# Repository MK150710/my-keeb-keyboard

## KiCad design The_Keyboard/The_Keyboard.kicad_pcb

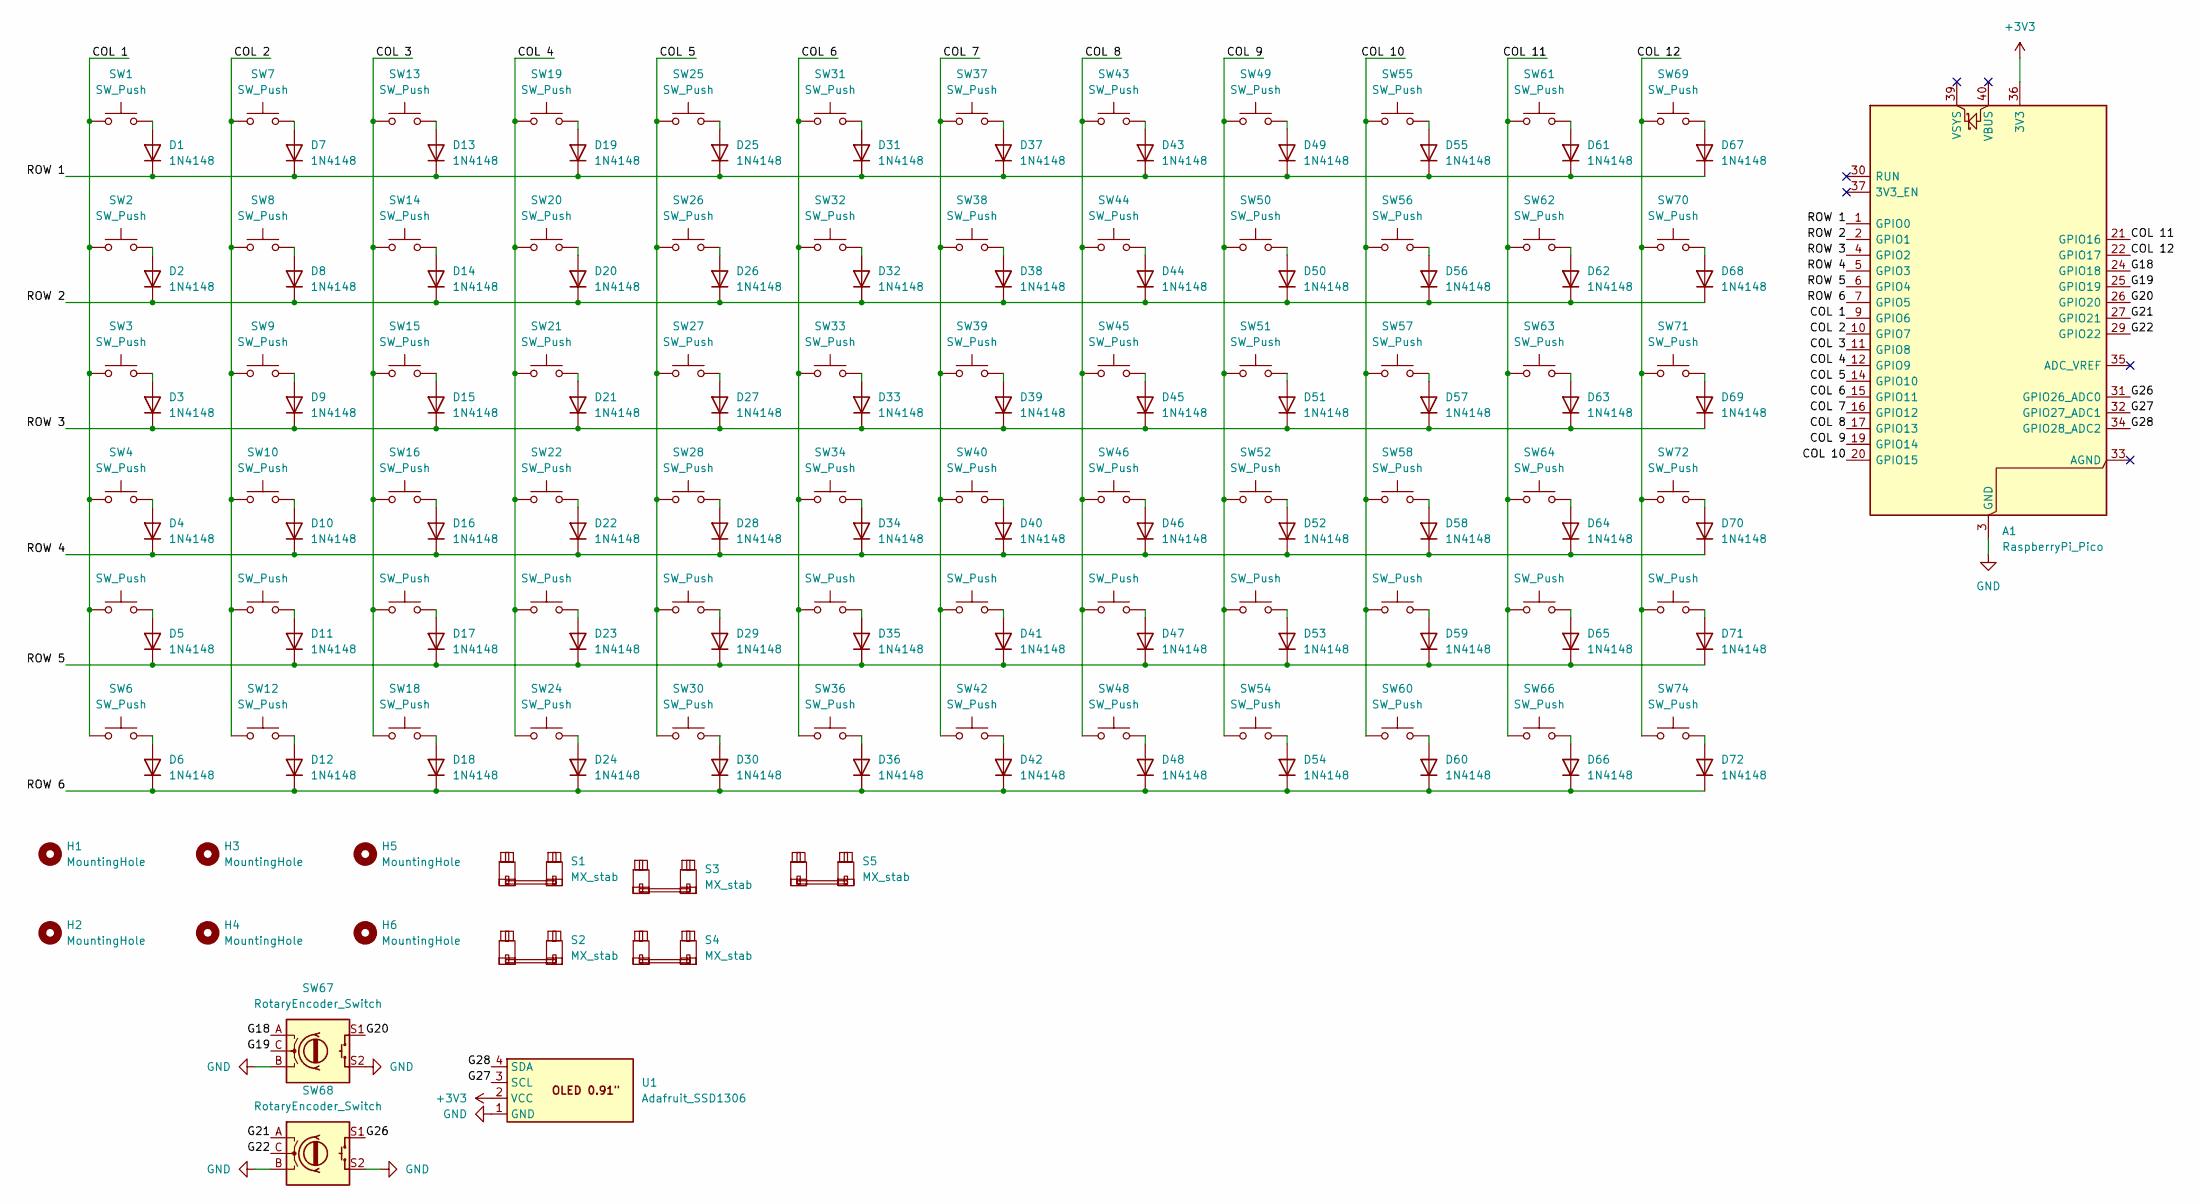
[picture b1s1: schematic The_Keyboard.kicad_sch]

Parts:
A1: RaspberryPi_Pico; RaspberryPi_Pico_Common_THT
D1, D2, D3, D4, D5, D6, D7, D8, D9, D10, D11, D12, D13, D14, D15, D16, D17, D18, D19, D20, D21, D22, D23, D24, D25, D26, D27, D28, D29, D30, D31, D32, D33, D34, D35, D36, D37, D38, D39, D40, D41, D42, D43, D44, D45, D46, D47, D48, D49, D50, D51, D52, D53, D54, D55, D56, D57, D58, D59, D60, D61, D62, D63, D64, D65, D66, D67, D68, D69, D70, D71, D72: 1N4148; D_DO-35_SOD27_P7.62mm_Horizontal
H1, H2, H3, H4, H5, H6: MountingHole; MountingHole_3.2mm_M3
S1, S3, S5: MX_stab; STAB_MX_2u
S2: MX_stab; STAB_MX_2.25u
S4: MX_stab; STAB_MX_P_6.25u
SW1, SW2, SW3, SW4, SW5, SW6, SW7, SW8, SW9, SW10, SW11, SW12, SW13, SW14, SW15, SW16, SW17, SW18, SW19, SW20, SW21, SW22, SW23, SW24, SW25, SW26, SW27, SW28, SW29, SW30, SW31, SW32, SW33, SW34, SW35, SW36, SW37, SW38, SW39, SW40, SW41, SW42, SW43, SW44, SW45, SW46, SW47, SW48, SW49, SW50, SW51, SW52, SW53, SW54, SW55, SW56, SW57, SW58, SW59, SW60, SW61, SW62, SW63, SW64, SW65, SW66, SW69, SW70, SW71, SW72, SW73, SW74: SW_Push; SW_MX_1u
SW67, SW68: RotaryEncoder_Switch; ROT_Alps_EC11E-Switch
U1: Adafruit_SSD1306; ER_OLEDM0.91_1x-I2C

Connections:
+3V3: A1.36 (3V3), U1.2 (VCC)
/COL 1: A1.9 (GPIO6), SW1.1, SW2.1, SW3.1, SW4.1, SW5.1, SW6.1
/COL 2: A1.10 (GPIO7), SW7.1, SW8.1, SW9.1, SW10.1, SW11.1, SW12.1
/COL 3: A1.11 (GPIO8), SW13.1, SW14.1, SW15.1, SW16.1, SW17.1, SW18.1
/COL 4: A1.12 (GPIO9), SW19.1, SW20.1, SW21.1, SW22.1, SW23.1, SW24.1
/COL 5: A1.14 (GPIO10), SW25.1, SW26.1, SW27.1, SW28.1, SW29.1, SW30.1
/COL 6: A1.15 (GPIO11), SW31.1, SW32.1, SW33.1, SW34.1, SW35.1, SW36.1
/COL 7: A1.16 (GPIO12), SW37.1, SW38.1, SW39.1, SW40.1, SW41.1, SW42.1
/COL 8: A1.17 (GPIO13), SW43.1, SW44.1, SW45.1, SW46.1, SW47.1, SW48.1
/COL 9: A1.19 (GPIO14), SW49.1, SW50.1, SW51.1, SW52.1, SW53.1, SW54.1
/COL 10: A1.20 (GPIO15), SW55.1, SW56.1, SW57.1, SW58.1, SW59.1, SW60.1
/COL 11: A1.21 (GPIO16), SW61.1, SW62.1, SW63.1, SW64.1, SW65.1, SW66.1
/COL 12: A1.22 (GPIO17), SW69.1, SW70.1, SW71.1, SW72.1, SW73.1, SW74.1
/G18: A1.24 (GPIO18), SW67.A
/G19: A1.25 (GPIO19), SW67.C
/G20: A1.26 (GPIO20), SW67.S1
/G21: A1.27 (GPIO21), SW68.A
/G22: A1.29 (GPIO22), SW68.C
/G26: A1.31 (GPIO26_ADC0), SW68.S1
/G27: A1.32 (GPIO27_ADC1), U1.3 (SCL)
/G28: A1.34 (GPIO28_ADC2), U1.4 (SDA)
/ROW 1: A1.1 (GPIO0), D1.1 (K), D7.1 (K), D13.1 (K), D19.1 (K), D25.1 (K), D31.1 (K), D37.1 (K), D43.1 (K), D49.1 (K), D55.1 (K), D61.1 (K), D67.1 (K)
/ROW 2: A1.2 (GPIO1), D2.1 (K), D8.1 (K), D14.1 (K), D20.1 (K), D26.1 (K), D32.1 (K), D38.1 (K), D44.1 (K), D50.1 (K), D56.1 (K), D62.1 (K), D68.1 (K)
/ROW 3: A1.4 (GPIO2), D3.1 (K), D9.1 (K), D15.1 (K), D21.1 (K), D27.1 (K), D33.1 (K), D39.1 (K), D45.1 (K), D51.1 (K), D57.1 (K), D63.1 (K), D69.1 (K)
/ROW 4: A1.5 (GPIO3), D4.1 (K), D10.1 (K), D16.1 (K), D22.1 (K), D28.1 (K), D34.1 (K), D40.1 (K), D46.1 (K), D52.1 (K), D58.1 (K), D64.1 (K), D70.1 (K)
/ROW 5: A1.6 (GPIO4), D5.1 (K), D11.1 (K), D17.1 (K), D23.1 (K), D29.1 (K), D35.1 (K), D41.1 (K), D47.1 (K), D53.1 (K), D59.1 (K), D65.1 (K), D71.1 (K)
/ROW 6: A1.7 (GPIO5), D6.1 (K), D12.1 (K), D18.1 (K), D24.1 (K), D30.1 (K), D36.1 (K), D42.1 (K), D48.1 (K), D54.1 (K), D60.1 (K), D66.1 (K), D72.1 (K)
GND: A1.3 (GND), A1.8 (GND), A1.13 (GND), A1.18 (GND), A1.23 (GND), A1.28 (GND), A1.38 (GND), SW67.B, SW67.S2, SW68.B, SW68.S2, U1.1 (GND)
unnamed: D1.2 (A), SW1.2
unnamed: D2.2 (A), SW2.2
unnamed: D3.2 (A), SW3.2
unnamed: D4.2 (A), SW4.2
unnamed: D5.2 (A), SW5.2
unnamed: D6.2 (A), SW6.2
unnamed: D7.2 (A), SW7.2
unnamed: D8.2 (A), SW8.2
unnamed: D9.2 (A), SW9.2
unnamed: D10.2 (A), SW10.2
unnamed: D11.2 (A), SW11.2
unnamed: D12.2 (A), SW12.2
unnamed: D13.2 (A), SW13.2
unnamed: D14.2 (A), SW14.2
unnamed: D15.2 (A), SW15.2
unnamed: D16.2 (A), SW16.2
unnamed: D17.2 (A), SW17.2
unnamed: D18.2 (A), SW18.2
unnamed: D19.2 (A), SW19.2
unnamed: D20.2 (A), SW20.2
unnamed: D21.2 (A), SW21.2
unnamed: D22.2 (A), SW22.2
unnamed: D23.2 (A), SW23.2
unnamed: D24.2 (A), SW24.2
unnamed: D25.2 (A), SW25.2
unnamed: D26.2 (A), SW26.2
unnamed: D27.2 (A), SW27.2
unnamed: D28.2 (A), SW28.2
unnamed: D29.2 (A), SW29.2
unnamed: D30.2 (A), SW30.2
unnamed: D31.2 (A), SW31.2
unnamed: D32.2 (A), SW32.2
unnamed: D33.2 (A), SW33.2
unnamed: D34.2 (A), SW34.2
unnamed: D35.2 (A), SW35.2
unnamed: D36.2 (A), SW36.2
unnamed: D37.2 (A), SW37.2
unnamed: D38.2 (A), SW38.2
unnamed: D39.2 (A), SW39.2
unnamed: D40.2 (A), SW40.2
unnamed: D41.2 (A), SW41.2
unnamed: D42.2 (A), SW42.2
unnamed: D43.2 (A), SW43.2
unnamed: D44.2 (A), SW44.2
unnamed: D45.2 (A), SW45.2
unnamed: D46.2 (A), SW46.2
unnamed: D47.2 (A), SW47.2
unnamed: D48.2 (A), SW48.2
unnamed: D49.2 (A), SW49.2
unnamed: D50.2 (A), SW50.2
unnamed: D51.2 (A), SW51.2
unnamed: D52.2 (A), SW52.2
unnamed: D53.2 (A), SW53.2
unnamed: D54.2 (A), SW54.2
unnamed: D55.2 (A), SW55.2
unnamed: D56.2 (A), SW56.2
unnamed: D57.2 (A), SW57.2
unnamed: D58.2 (A), SW58.2
unnamed: D59.2 (A), SW59.2
unnamed: D60.2 (A), SW60.2
unnamed: D61.2 (A), SW61.2
unnamed: D62.2 (A), SW62.2
unnamed: D63.2 (A), SW63.2
unnamed: D64.2 (A), SW64.2
unnamed: D65.2 (A), SW65.2
unnamed: D66.2 (A), SW66.2
unnamed: D67.2 (A), SW69.2
unnamed: D68.2 (A), SW70.2
unnamed: D69.2 (A), SW71.2
unnamed: D70.2 (A), SW72.2
unnamed: D71.2 (A), SW73.2
unnamed: D72.2 (A), SW74.2

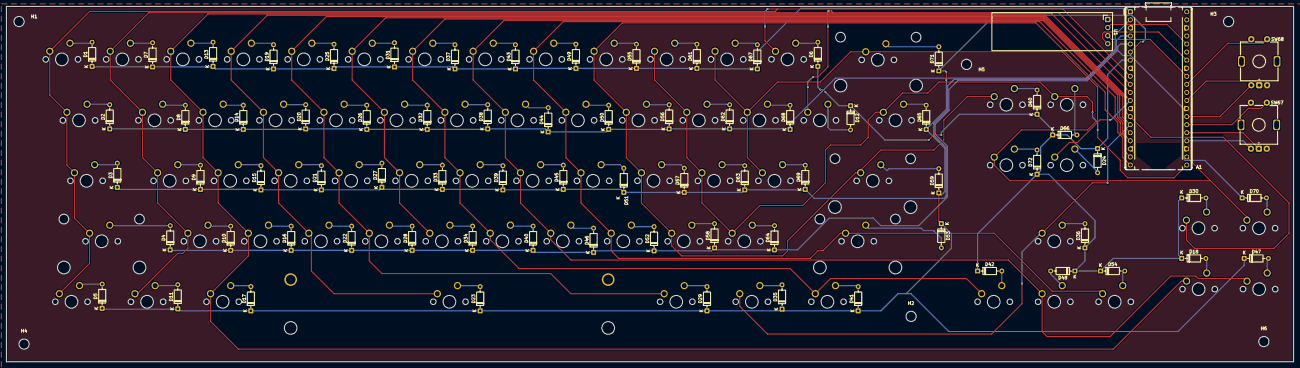
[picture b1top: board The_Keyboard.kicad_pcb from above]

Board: 2 copper layers, 405.4 x 111.9 mm, 159 parts (0 on the bottom side), 100 nets.
